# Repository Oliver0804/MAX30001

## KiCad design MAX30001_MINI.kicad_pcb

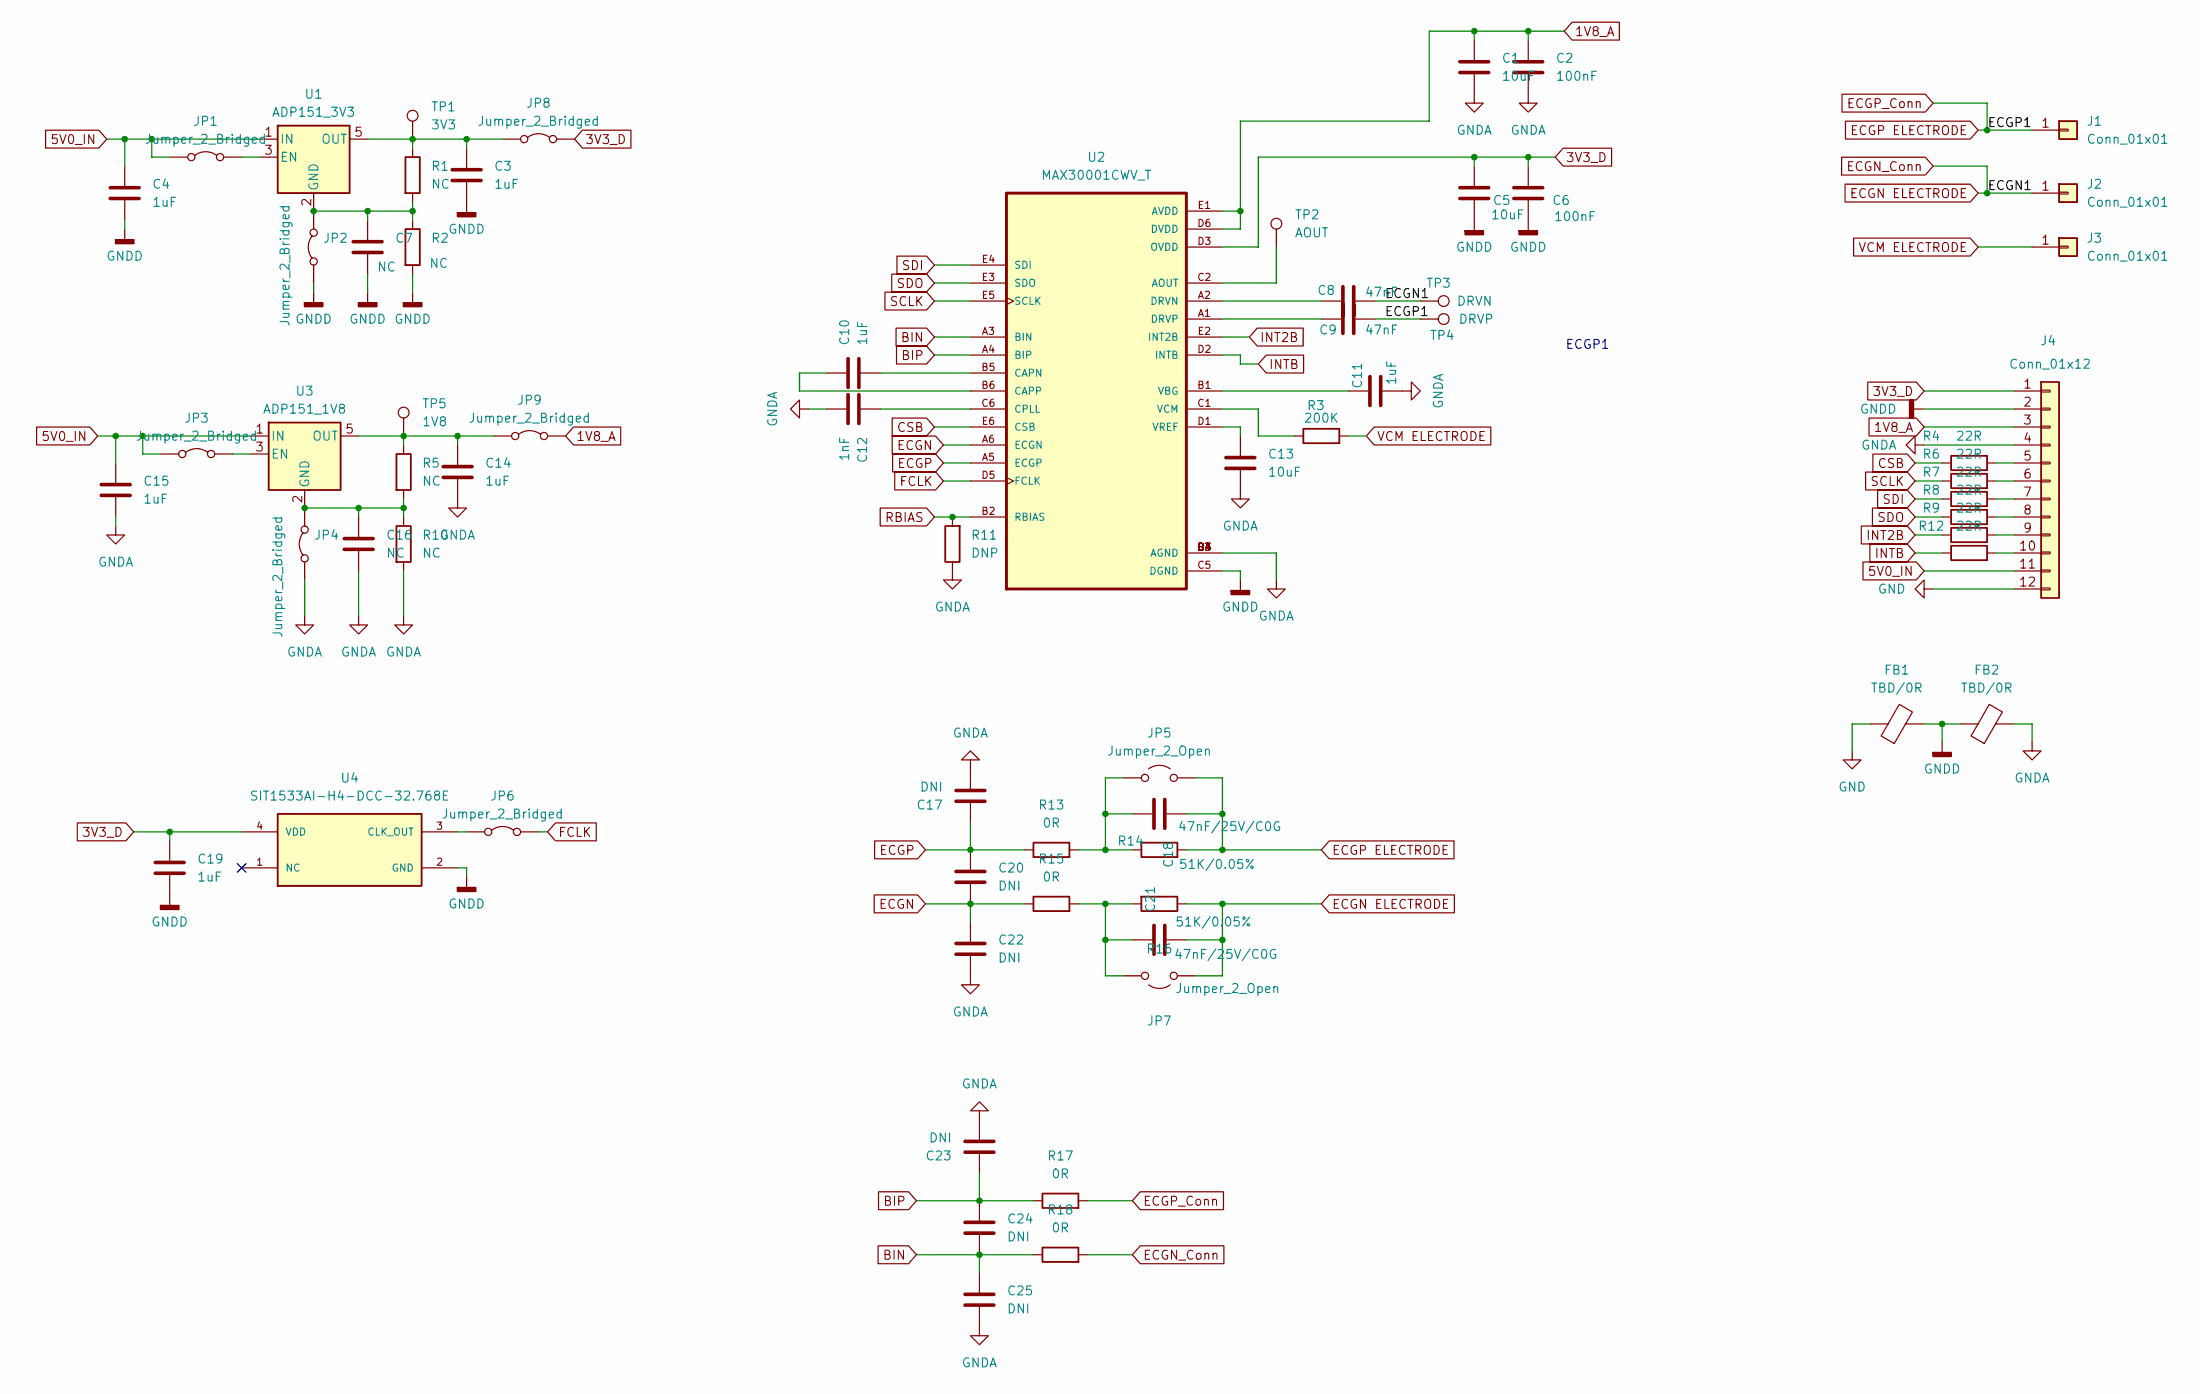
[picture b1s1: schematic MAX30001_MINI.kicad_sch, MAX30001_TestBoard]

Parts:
C1, C5, C13: 10uF; C_0603_1608Metric
C2, C6: 100nF; C_0603_1608Metric
C3, C4, C10, C11, C14, C15, C19: 1uF; C_0603_1608Metric
C7, C16: NC; C_0603_1608Metric
C8, C9: 47nF; C_0603_1608Metric
C12: 1nF; C_0603_1608Metric
C17, C20, C22, C23, C24, C25: DNI; C_0603_1608Metric
C18, C21: 47nF/25V/C0G; C_0603_1608Metric
FB1, FB2: TBD/0R; R_0603_1608Metric
J1, J2, J3: Conn_01x01; Mounting_Wuerth_WA-SMSI-M3_H6mm_9774060360
J4: Conn_01x12; PinHeader_1x12_P2.54mm_Vertical
JP1, JP2, JP3, JP4, JP6, JP8, JP9: Jumper_2_Bridged; SolderJumper-2_P1.3mm_Bridged2Bar_RoundedPad1.0x1.5mm
JP5, JP7: Jumper_2_Open; SolderJumper-2_P1.3mm_Open_RoundedPad1.0x1.5mm
R1, R2, R5, R10: NC; R_0603_1608Metric
R3: 200K; R_0603_1608Metric
R4, R6, R7, R8, R9, R12: 22R; R_0603_1608Metric
R11: DNP; R_0603_1608Metric
R13, R15, R17, R18: 0R; R_0603_1608Metric
R14, R16: 51K/0.05%; R_0603_1608Metric
TP1: 3V3; TestPoint_THTPad_1.0x1.0mm_Drill0.5mm
TP2: AOUT; TestPoint_THTPad_1.0x1.0mm_Drill0.5mm
TP3: DRVN; TestPoint_THTPad_1.0x1.0mm_Drill0.5mm
TP4: DRVP; TestPoint_THTPad_1.0x1.0mm_Drill0.5mm
TP5: 1V8; TestPoint_THTPad_1.0x1.0mm_Drill0.5mm
U1: ADP151_3V3; TSOT-23-5
U2: MAX30001CWV_T; BGA30N50P5X6_274X292X69N
U3: ADP151_1V8; TSOT-23-5
U4: SIT1533AI-H4-DCC-32.768E; SIT1533AI_2X1.2MM

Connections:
1V8_A: C1.1, C2.1, J4.3, JP9.2 (B), U2.D6 (DVDD), U2.E1 (AVDD)
3V3_D: C5.1, C6.1, C19.1, J4.1, JP8.2 (B), U2.D3 (OVDD), U4.4 (VDD)
5V0_IN: C4.1, C15.1, J4.11, JP1.1 (A), JP3.1 (A), U1.1 (IN), U3.1 (IN)
BIN: C24.2, C25.1, R18.1, U2.A3 (BIN)
BIP: C23.1, C24.1, R17.1, U2.A4 (BIP)
CSB: R4.1, U2.E6 (CSB)
ECGN: C20.2, C22.1, R15.1, U2.A6 (ECGN)
ECGN ELECTRODE: C8.2, C21.2, J2.1, JP7.1 (A), R16.1, R18.2, TP3.1
ECGP: C17.1, C20.1, R13.1, U2.A5 (ECGP)
ECGP ELECTRODE: C9.2, C18.1, J1.1, JP5.2 (B), R14.2, R17.2, TP4.1
FCLK: JP6.2 (B), U2.D5 (FCLK)
GND: FB1.1, J4.12
GNDA: C1.2, C2.2, C11.2, C12.2, C13.2, C14.2, C15.2, C16.2, C17.2, C22.2, C23.2, C25.2, FB2.2, J4.4, JP4.1 (A), R10.2, R11.1, U2.B3 (AGND), U2.B4 (AGND), U2.C3 (AGND), U2.C4 (AGND), U2.D4 (AGND)
GNDD: C3.2, C4.2, C5.2, C6.2, C7.2, C19.2, FB1.2, FB2.1, J4.2, JP2.1 (A), R2.2, U2.C5 (DGND), U4.2 (GND)
INT2B: R9.1, U2.E2 (INT2B)
INTB: R12.1, U2.D2 (INTB)
unnamed: J4.5, R4.2
unnamed: J4.6, R6.2
unnamed: J4.7, R7.2
unnamed: J4.8, R8.2
unnamed: J4.9, R9.2
unnamed: J4.10, R12.2
unnamed: JP1.2 (B), U1.3 (EN)
unnamed: C7.1, JP2.2 (B), R1.2, R2.1, U1.2 (GND)
unnamed: JP3.2 (B), U3.3 (EN)
unnamed: C16.1, JP4.2 (B), R5.2, R10.1, U3.2 (GND)
unnamed: C18.2, JP5.1 (A), R13.2, R14.1
unnamed: JP6.1 (A), U4.3 (CLK_OUT)
unnamed: C21.1, JP7.2 (B), R15.2, R16.2
unnamed: C3.1, JP8.1 (A), R1.1, TP1.1, U1.5 (OUT)
unnamed: C14.1, JP9.1 (A), R5.1, TP5.1, U3.5 (OUT)
unnamed: TP2.1, U2.C2 (AOUT)
unnamed: C10.2, U2.B5 (CAPN)
unnamed: C10.1, U2.B6 (CAPP)
unnamed: C12.1, U2.C6 (CPLL)
unnamed: C8.1, U2.A2 (DRVN)
unnamed: C9.1, U2.A1 (DRVP)
unnamed: C11.1, U2.B1 (VBG)
unnamed: R3.1, U2.C1 (VCM)
unnamed: C13.1, U2.D1 (VREF)
RBIAS: R11.2, U2.B2 (RBIAS)
SCLK: R6.1, U2.E5 (SCLK)
SDI: R7.1, U2.E4 (SDI)
SDO: R8.1, U2.E3 (SDO)
VCM ELECTRODE: J3.1, R3.2

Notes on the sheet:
ECGP1

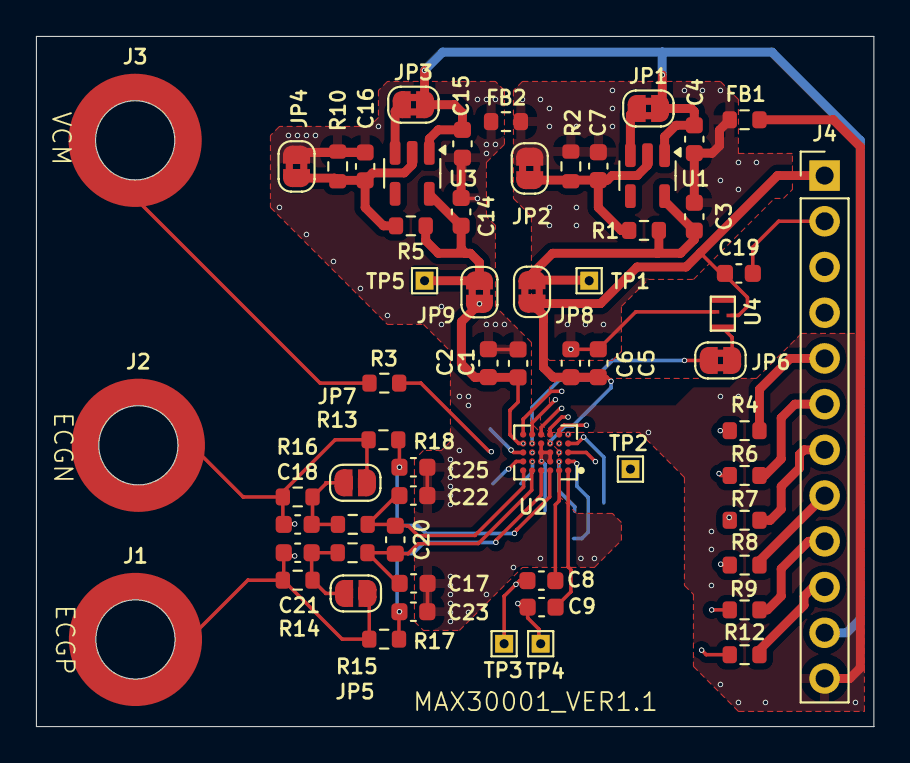
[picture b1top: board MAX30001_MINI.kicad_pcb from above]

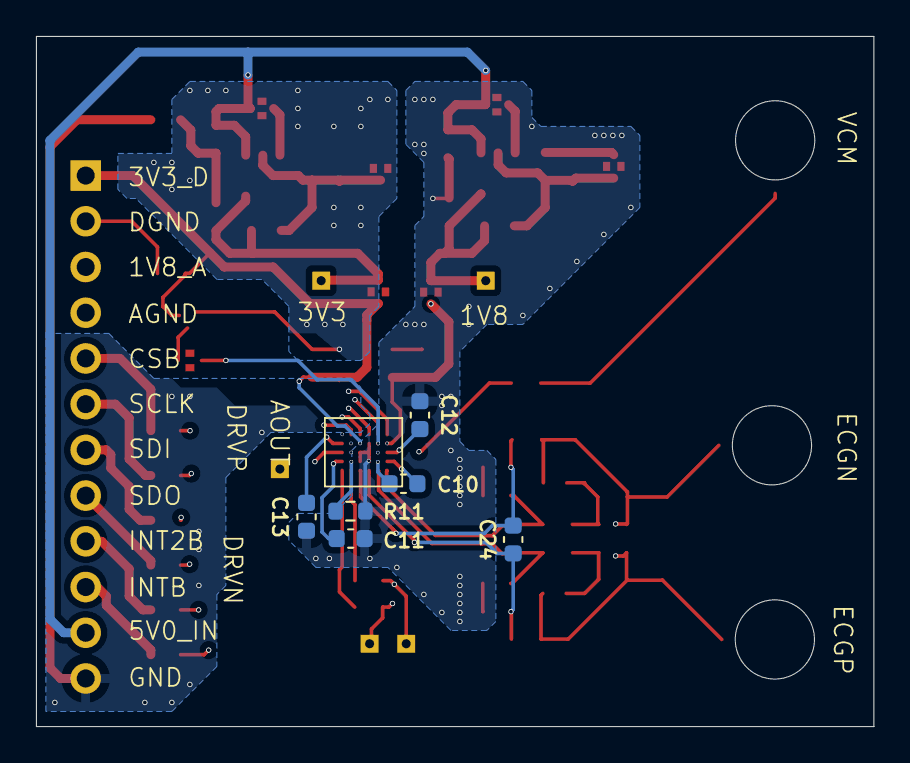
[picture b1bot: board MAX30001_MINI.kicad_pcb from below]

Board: 4 copper layers, 46.5 x 38.3 mm, 67 parts (6 on the bottom side), 45 nets.

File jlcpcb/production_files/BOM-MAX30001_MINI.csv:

Comment,Designator,Footprint,LCSC
100nF,"C2,C6",C_0603_1608Metric,C14663
1uF,"C10,C11,C14,C15,C19,C3,C4",C_0603_1608Metric,C15849
1nF,C12,C_0603_1608Metric,C1588
47nF,"C8,C9",C_0603_1608Metric,C1622
10uF,"C1,C13,C5",C_0603_1608Metric,C19702
0R,"R13,R15,R17,R18",R_0603_1608Metric,C21189
47nF/25V/C0G,"C18,C21",C_0603_1608Metric,C21812
22R,"R12,R4,R6,R7,R8,R9",R_0603_1608Metric,C23345
200K,R3,R_0603_1608Metric,C25811
MAX30001CWV_T,U2,BGA30N50P5X6_274X292X69N,C2650384
51K/0.05%,"R14,R16",R_0603_1608Metric,C336807
ADP151_3V3,U1,TSOT-23-5,C61006
ADP151_3V3,U3,TSOT-23-5,C658763
DNI,C25,C_0603_1608Metric,
DRVN,TP3,TestPoint_THTPad_1.0x1.0mm_Drill0.5mm,
DNI,C20,C_0603_1608Metric,
SIT1533AI-H4-DCC-32.768E,U4,SIT1533AI_2X1.2MM,
Conn_01x01,J1,Mounting_Wuerth_WA-SMSI-M3_H6mm_9774060360,
NC,R10,R_0603_1608Metric,
DRVP,TP4,TestPoint_THTPad_1.0x1.0mm_Drill0.5mm,
Conn_01x12,J4,PinHeader_1x12_P2.54mm_Vertical,
DNI,C24,C_0603_1608Metric,
TBD/0R,FB1,R_0603_1608Metric,
NC,R5,R_0603_1608Metric,
Jumper_2_Open,JP7,SolderJumper-2_P1.3mm_Open_RoundedPad1.0x1.5mm,
Jumper_2_Open,JP5,SolderJumper-2_P1.3mm_Open_RoundedPad1.0x1.5mm,
NC,R1,R_0603_1608Metric,
DNI,C23,C_0603_1608Metric,
DNI,C22,C_0603_1608Metric,
NC,C7,C_0603_1608Metric,
Conn_01x01,J2,Mounting_Wuerth_WA-SMSI-M3_H6mm_9774060360,
3V3,TP1,TestPoint_THTPad_1.0x1.0mm_Drill0.5mm,
Jumper_2_Bridged,JP8,SolderJumper-2_P1.3mm_Bridged2Bar_RoundedPad1.0x1.5mm,
Conn_01x01,J3,Mounting_Wuerth_WA-SMSI-M3_H6mm_9774060360,
AOUT,TP2,TestPoint_THTPad_1.0x1.0mm_Drill0.5mm,
Jumper_2_Bridged,JP9,SolderJumper-2_P1.3mm_Bridged2Bar_RoundedPad1.0x1.5mm,
Jumper_2_Bridged,JP1,SolderJumper-2_P1.3mm_Bridged2Bar_RoundedPad1.0x1.5mm,
Jumper_2_Bridged,JP4,SolderJumper-2_P1.3mm_Bridged2Bar_RoundedPad1.0x1.5mm,
Jumper_2_Bridged,JP3,SolderJumper-2_P1.3mm_Bridged2Bar_RoundedPad1.0x1.5mm,
DNP,R11,R_0603_1608Metric,
Jumper_2_Bridged,JP6,SolderJumper-2_P1.3mm_Bridged2Bar_RoundedPad1.0x1.5mm,
Jumper_2_Bridged,JP2,SolderJumper-2_P1.3mm_Bridged2Bar_RoundedPad1.0x1.5mm,
1V8,TP5,TestPoint_THTPad_1.0x1.0mm_Drill0.5mm,
TBD/0R,FB2,R_0603_1608Metric,
NC,C16,C_0603_1608Metric,
NC,R2,R_0603_1608Metric,
DNI,C17,C_0603_1608Metric,

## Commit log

2024-10-09 [fix] Fixed issue DRVP/DRVN net nodes not connected
    Fixed the issue where DRVP/DRVN net nodes were not connected.
